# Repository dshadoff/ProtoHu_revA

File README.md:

# ProtoHu_revA

ProtoHu was a prototype HuCard I designed, to test the viability of making a
PC Engine HuCard from PC boards.

This version uses an inexpensive 4-megabit Flash memory (SST39SF040), and can
also be programmed by a regular DIP-based EPROM programmer.  Unlike designs such
as the TurboEverdrive, this card is intended for a single program at a time,
and will boot directly to the code, without entering a menu system.

This board was the predecessor to the Megavault design
[github.com/dshadoff/Megavault](https://github.com/dshadoff/Megavault).

As the NOR Flash is rated for 100 years and 100,000 write cycles, there is no
concern about lifetime under the usage in this application.

I designed the boards using the free version of EAGLE (2-layer, less than 100mm
on both X- and Y-axes).  The gerbers are included in this repository as well as
a small EAGLE library of part footprints.

If you decide to get these boards made, I recommend selecting the ENIG option,
which provides a very thin coating of gold plating on all of the exposed metal
areas.  This provides a more flat surface for soldering the memory chip, and
prevents corrossion to some degree over time.  ENIG is by no means comparable
to "hard gold", but it is better than an exposed copper or solder-based surface.

As the boards themselves don't provide to omuch information about how to use them,
here are a few pictures of the orientation of various parts:

## Chip Mounting Orientation:

## Header Mounting Orientation:

## Orientation when programming:

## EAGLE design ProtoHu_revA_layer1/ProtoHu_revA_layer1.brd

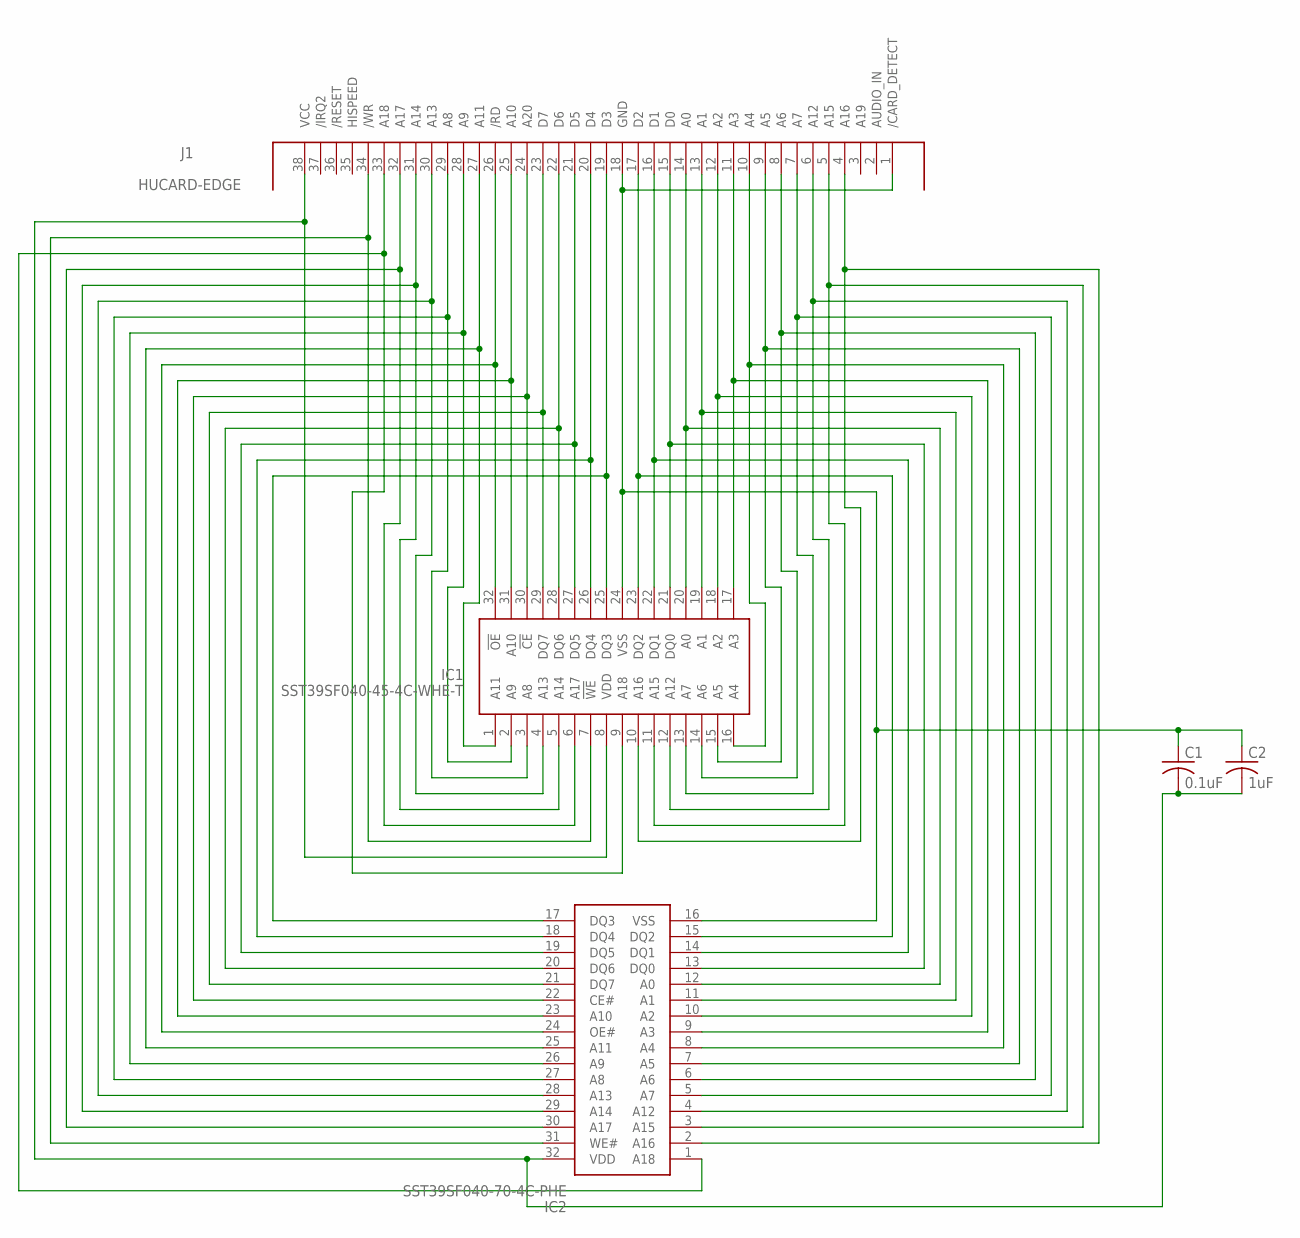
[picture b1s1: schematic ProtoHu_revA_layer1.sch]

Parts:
C1: 0.1uF; C0603
C2: 1uF; C0603
IC1: SST39SF040-45-4C-WHE-T; SOP50P1400X120-32N
IC2: SST39SF040-70-4C-PHE; DIP1556W56P254L4191H508Q32N
J1: HUCARD-EDGE

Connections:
GND: C1.1, C2.1, IC1.24 (VSS), IC2.16 (VSS), J1.1 (/CARD_DETECT), J1.18 (GND)
unnamed: IC1.14 (A6), IC2.6 (A6), J1.8 (A6)
unnamed: IC1.13 (A7), IC2.5 (A7), J1.7 (A7)
unnamed: IC1.12 (A12), IC2.4 (A12), J1.6 (A12)
unnamed: IC1.25 (DQ3), IC2.17 (DQ3), J1.19 (D3)
unnamed: IC1.26 (DQ4), IC2.18 (DQ4), J1.20 (D4)
unnamed: IC1.27 (DQ5), IC2.19 (DQ5), J1.21 (D5)
unnamed: IC1.11 (A15), IC2.3 (A15), J1.5 (A15)
unnamed: IC1.10 (A16), IC2.2 (A16), J1.4 (A16)
unnamed: IC1.23 (DQ2), IC2.15 (DQ2), J1.17 (D2)
unnamed: IC1.22 (DQ1), IC2.14 (DQ1), J1.16 (D1)
unnamed: IC1.21 (DQ0), IC2.13 (DQ0), J1.15 (D0)
unnamed: IC1.7 (!WE), IC2.31 (WE#), J1.34 (/WR)
unnamed: IC1.28 (DQ6), IC2.20 (DQ6), J1.22 (D6)
unnamed: IC1.29 (DQ7), IC2.21 (DQ7), J1.23 (D7)
unnamed: IC1.30 (!CE), IC2.22 (CE#), J1.24 (A20)
unnamed: IC1.31 (A10), IC2.23 (A10), J1.25 (A10)
unnamed: IC1.32 (!OE), IC2.24 (OE#), J1.26 (/RD)
unnamed: IC1.1 (A11), IC2.25 (A11), J1.27 (A11)
unnamed: IC1.2 (A9), IC2.26 (A9), J1.28 (A9)
unnamed: IC1.20 (A0), IC2.12 (A0), J1.14 (A0)
unnamed: IC1.19 (A1), IC2.11 (A1), J1.13 (A1)
unnamed: IC1.18 (A2), IC2.10 (A2), J1.12 (A2)
unnamed: IC1.17 (A3), IC2.9 (A3), J1.11 (A3)
unnamed: IC1.3 (A8), IC2.27 (A8), J1.29 (A8)
unnamed: IC1.4 (A13), IC2.28 (A13), J1.30 (A13)
unnamed: IC1.5 (A14), IC2.29 (A14), J1.31 (A14)
unnamed: IC1.6 (A17), IC2.30 (A17), J1.32 (A17)
unnamed: IC1.16 (A4), IC2.8 (A4), J1.10 (A4)
unnamed: IC1.15 (A5), IC2.7 (A5), J1.9 (A5)
unnamed: IC1.9 (A18), IC2.1 (A18), J1.33 (A18)
VCC: C1.2, C2.2, IC1.8 (VDD), IC2.32 (VDD), J1.38 (VCC)

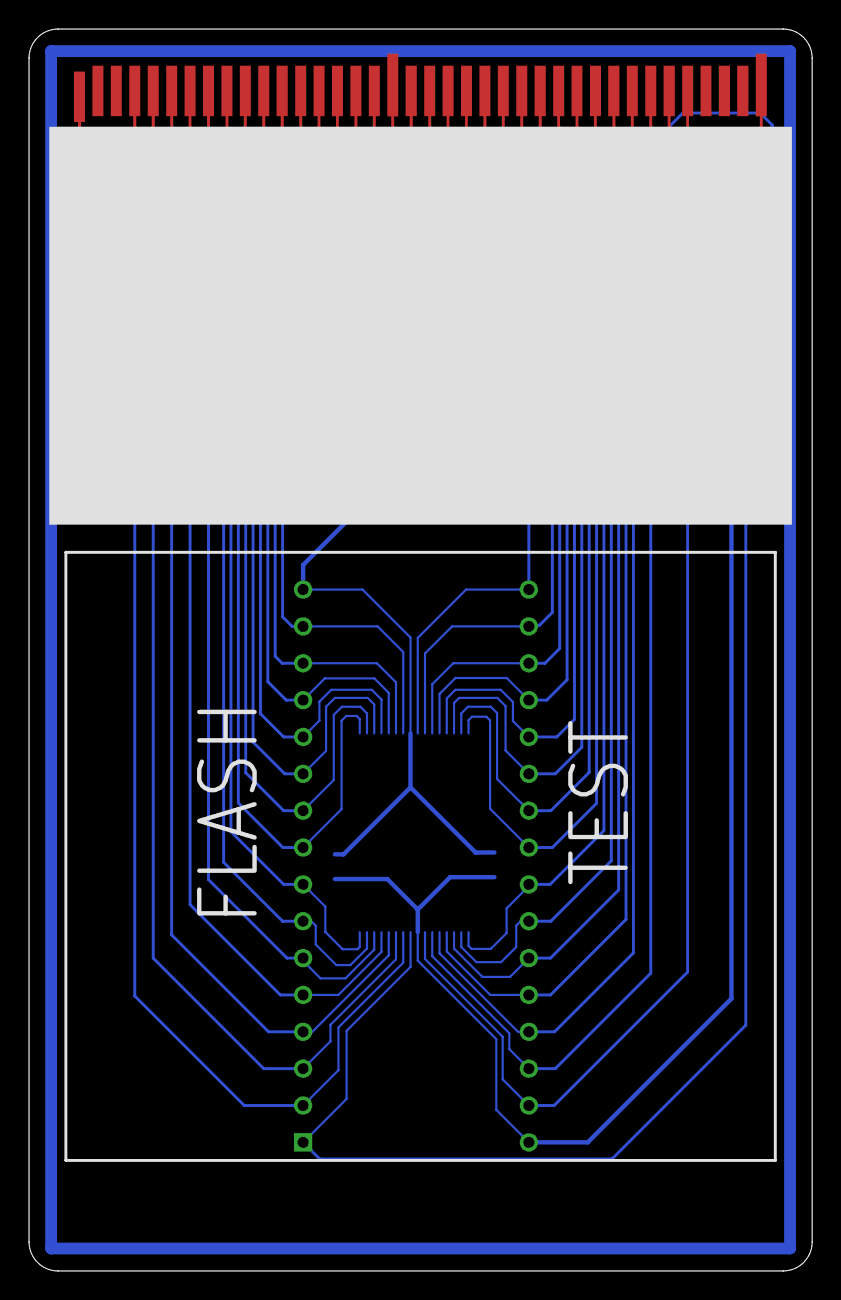
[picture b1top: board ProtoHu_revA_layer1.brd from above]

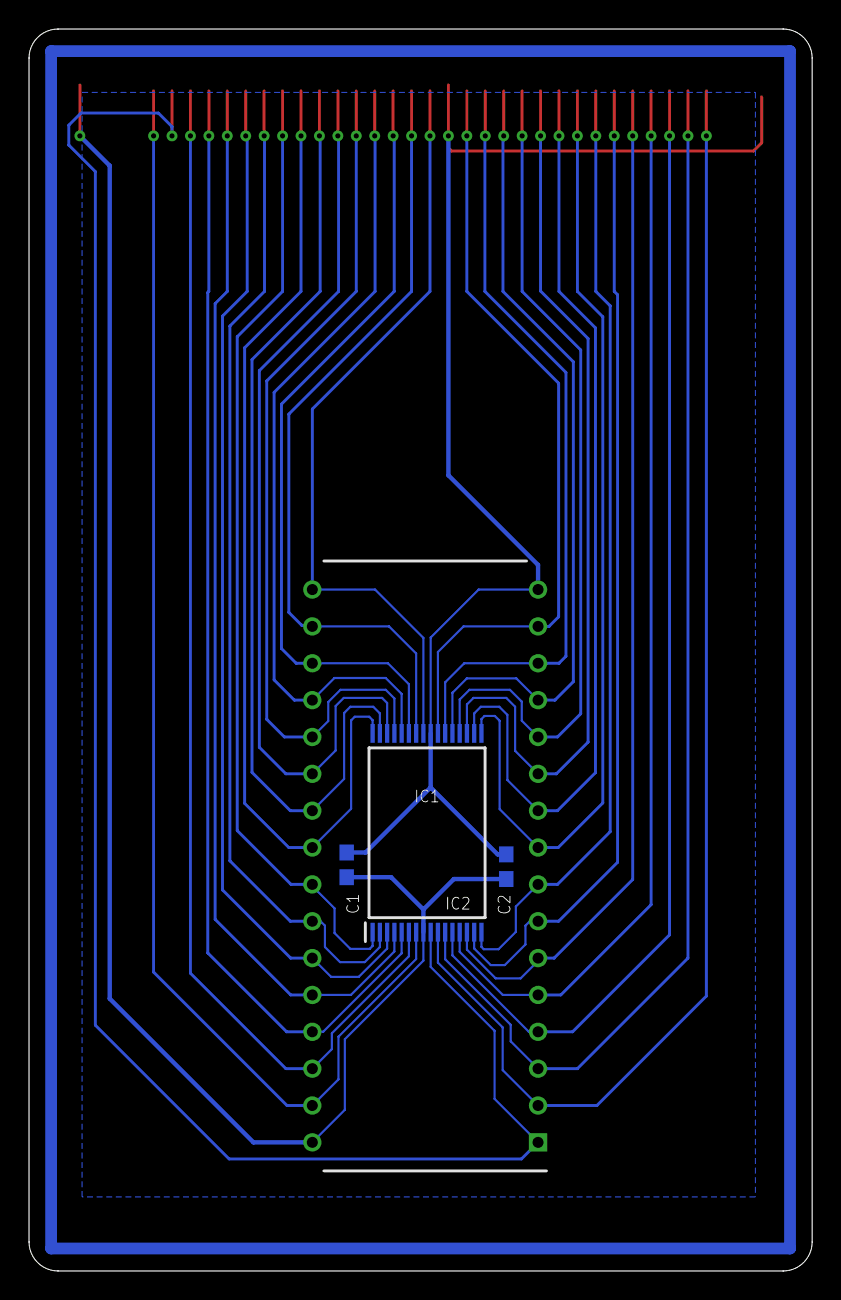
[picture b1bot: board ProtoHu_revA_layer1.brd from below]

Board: 2 copper layers, 54.0 x 85.6 mm, 5 parts (4 on the bottom side), 32 nets.

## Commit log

2020-05-02 Initial Commit
    Initial Commit
2020-05-02 Fix image location
    Fix image location
2020-05-02 Minor edits to README
    Minor edits to README
